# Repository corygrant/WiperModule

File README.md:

# WiperModule
Simple relay board to control automotive wiper motor from digital outputs

This board was created when I needed a way to control a MK2 VW wiper motor using outputs from my PDM.

Many PDMs require either external relays to drive wiper motors or use specific outputs designed to handle the wiper motor braking functionality.

Rather than include this specific feature on the PDM, I opted to create a simple relay board that can be placed inbetween the PDM and the wiper motor.

This setup also allows me to use 1 high current output to drive the motor at low speed or high speed, and one low current output to control that speed.

Wires are connected to the board using Deutsch DT 4 pin connectors 

# Wiring

 Pin | Function
 ----| --------- 
 1   | Fast Input
 2   | Ground
 3   | Park Switch
 4   | Slow Input

# Connection Table
Slow Input Level | Fast Input Level | Slow Output Connection | Fast Output Connection
---------- | ---------- | ----------- | -----------
L | L | Ground | Not Connected
H | L | Slow Input | Not Connected
L | H | Ground | Not Connected
H | H | Not Connected | Slow Input

# Renderings

 # [Store](https://dingo-electronics.square.site/product/wipermodule/4)

 # Disclaimer
 Please note that this product has been designed by a hobbyist, not a professional. It is intended for off-road and testing use only. Users should operate the product at their own discretion and risk. The designer explicitly disclaims any responsibility for damage or injury that may result from the use of this product.

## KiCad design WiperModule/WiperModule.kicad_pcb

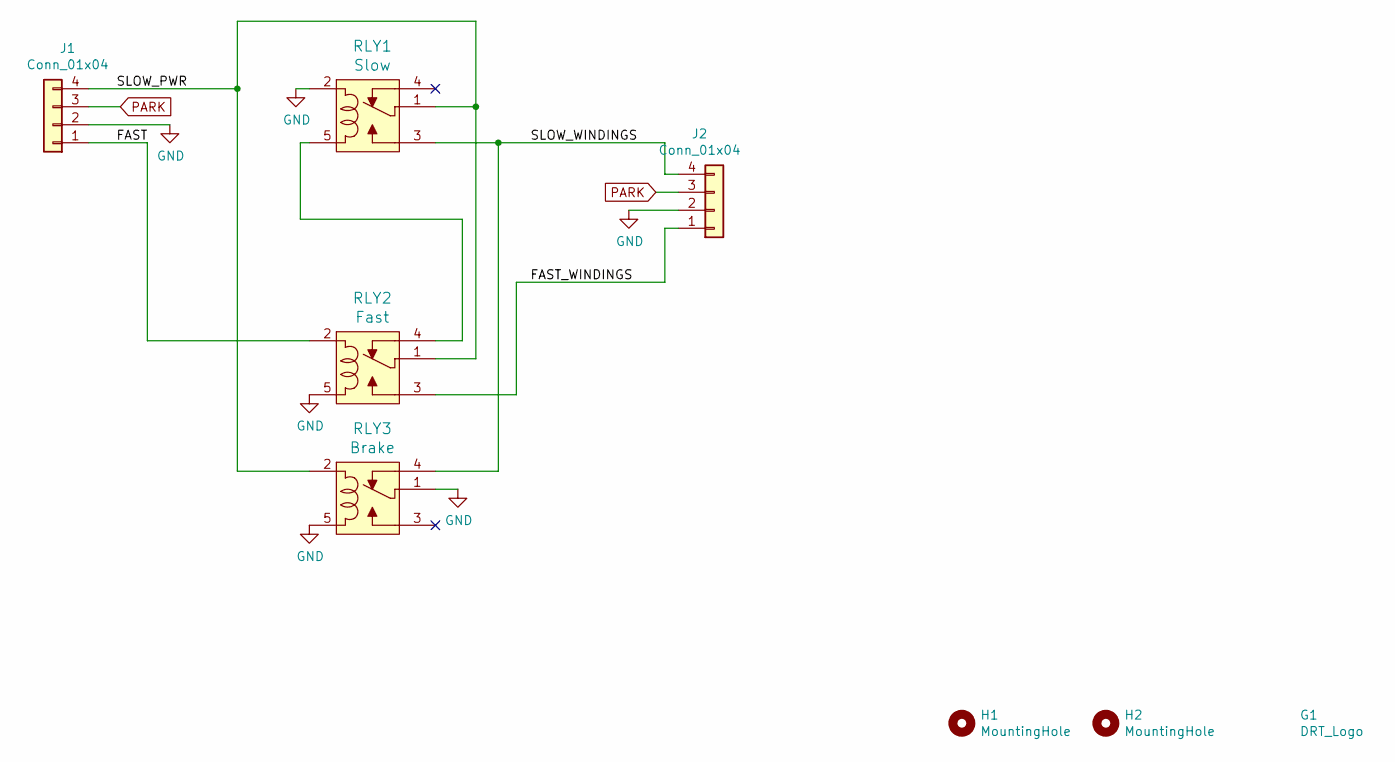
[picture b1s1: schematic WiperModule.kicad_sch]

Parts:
G1: DRT_Logo; DRTLogo
H1, H2: MountingHole; MountingHole_4.3mm_M4_DIN965_Pad
J1, J2: Conn_01x04; DTF13-4P; Digi-Key_PN 1734-1646-ND
RLY1: Slow; Relay_JSM1-12V-5; MPN JSM1-12V-5; Digi-Key_PN Z2617-ND
RLY2: Fast; Relay_JSM1-12V-5; MPN JSM1-12V-5; Digi-Key_PN Z2617-ND
RLY3: Brake; Relay_JSM1-12V-5; MPN JSM1-12V-5; Digi-Key_PN Z2617-ND

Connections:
/FAST: J1.1, RLY2.2
/FAST_WINDINGS: J2.1, RLY2.3 (NO)
/SLOW_PWR: J1.4, RLY1.1 (COM), RLY2.1 (COM), RLY3.2
/SLOW_WINDINGS: J2.4, RLY1.3 (NO), RLY3.4 (NC)
GND: J1.2, J2.2, RLY1.2, RLY2.5, RLY3.1 (COM), RLY3.5
unnamed: RLY1.5, RLY2.4 (NC)
PARK: J1.3, J2.3

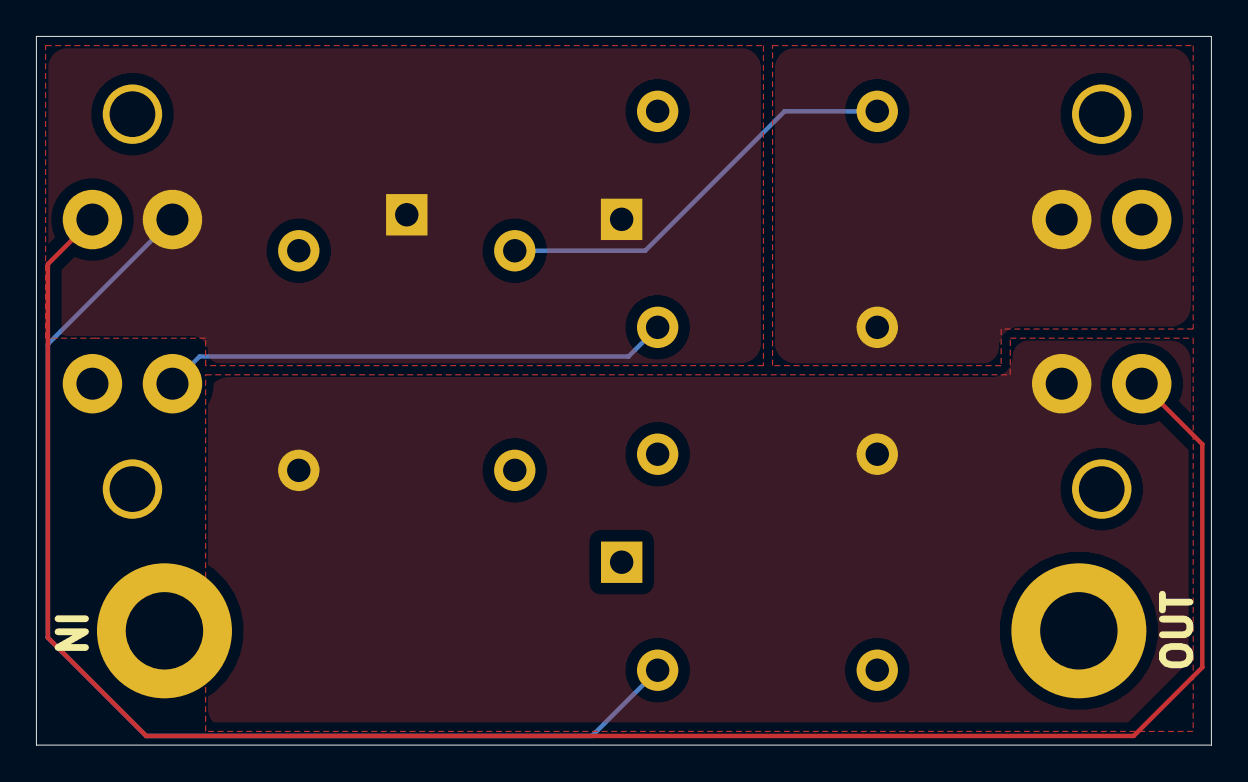
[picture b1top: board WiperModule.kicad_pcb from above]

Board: 2 copper layers, 65.3 x 39.4 mm, 8 parts (1 on the bottom side), 7 nets.

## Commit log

2021-04-10 Reorganizing files
2024-04-03 Updated to latest Kicad, images and added gitignore
2024-09-06 Update to Kicad 8
